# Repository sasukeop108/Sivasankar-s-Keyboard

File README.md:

# Sivasankar's keyboard
One day, I was thinking about making a custom keyboard which would be suitable for me from scratch but that was too costly. After i joined hackclub's stasis i thought why not to build our keyboard as the stasis event funds us. So i started making a custom 75 percent keyboard from scratch using fusion 360 and kicad. I used the layout keycool 84 which had 84 keys in it.
# Built keyboard

# Layout
.png)
# CAD

# PCB

# SCHEMATIC

# BOM
| Name | Purpose | Cost Per Item (USD) | Quantity | Total (USD) | Link | Distributor |
| :--- | :--- | :--- | :--- | :--- | :--- | :--- |
| 3d case | for housing keyboard | 8.50 | 1 | 8.50 | | printing legion |
| switches | for input to raspberry pi pico | 2.14 | 9 | 19.26 | [Cosmic Byte](https://www.thecosmicbyte.com/product/gateron-mechanical-switches-compatible-with-cosmic-byte-hot-swappable-keyboards-qty-1pc/) | cosmic byte |
| raspberry pi pico | for controlling everything | 0.00 | 1 | 0.00 | | self sourced |
| custom pcb | for soldering all components on | 40.65 | 1 | 40.65 | | jlcpcb |
| stabilizers | for bigger keycaps | 17.05 | 1 | 17.05 | [StacksKB](https://stackskb.com) | stackskb |
| keycaps | keys for typing | 13.89 | 1 | 13.89 | [StacksKB](https://stackskb.com/store/veekos-gradient-keycaps-cherry-profile-135-keys/) | stackskb |
| **Grand Total** | | | | **99.35** | | |
# Flashing instructions
download the keyboard.py from, the firmware folder and import it into circuit python select the com ports and youre ready to flash the code.

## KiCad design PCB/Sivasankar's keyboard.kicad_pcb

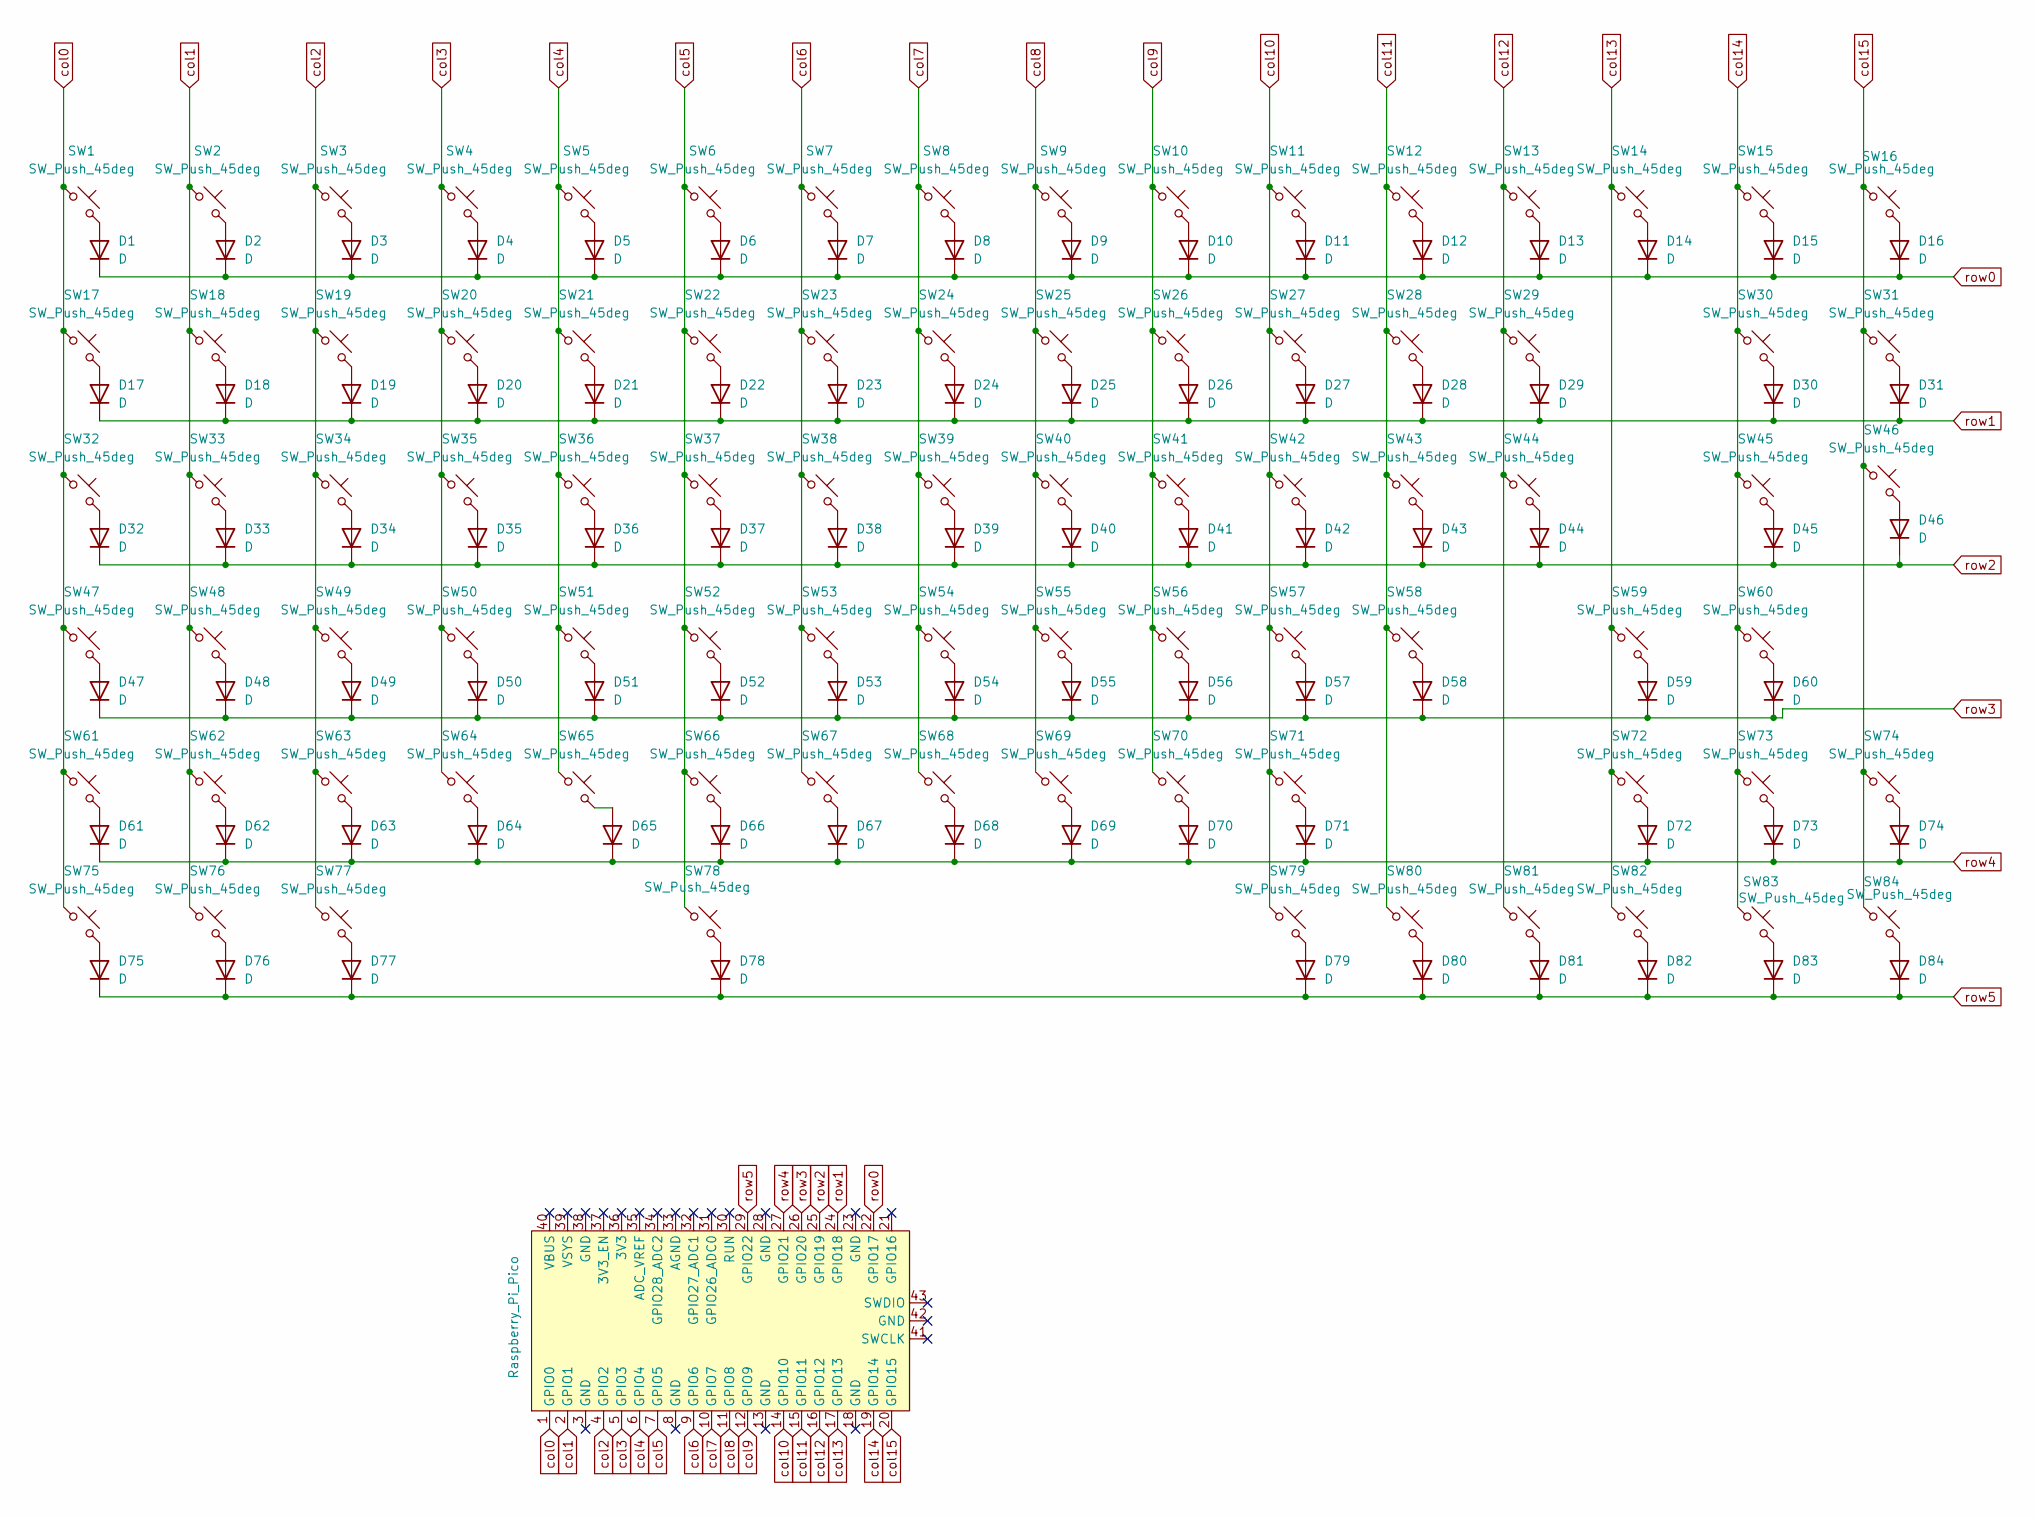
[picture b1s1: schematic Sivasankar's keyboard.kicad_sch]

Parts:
D1, D2, D3, D4, D5, D6, D7, D8, D9, D10, D11, D12, D13, D14, D15, D16, D17, D18, D19, D20, D21, D22, D23, D24, D25, D26, D27, D28, D29, D30, D31, D32, D33, D34, D35, D36, D37, D38, D39, D40, D41, D42, D43, D44, D45, D46, D47, D48, D49, D50, D51, D52, D53, D54, D55, D56, D57, D58, D59, D60, D61, D62, D63, D64, D65, D66, D67, D68, D69, D70, D71, D72, D73, D74, D75, D76, D77, D78, D79, D80, D81, D82, D83, D84: D; D_DO-35_SOD27_P7.62mm_Horizontal
SW1, SW2, SW3, SW4, SW5, SW6, SW7, SW8, SW9, SW10, SW11, SW12, SW13, SW14, SW15, SW16, SW17, SW18, SW19, SW20, SW21, SW22, SW23, SW24, SW25, SW26, SW27, SW28, SW29, SW30, SW31, SW32, SW33, SW34, SW35, SW36, SW37, SW38, SW39, SW40, SW41, SW42, SW43, SW44, SW45, SW46, SW47, SW48, SW49, SW50, SW51, SW52, SW53, SW54, SW55, SW56, SW57, SW58, SW59, SW60, SW61, SW62, SW63, SW64, SW65, SW66, SW67, SW68, SW69, SW70, SW71, SW72, SW73, SW74, SW75, SW76, SW77, SW78, SW79, SW80, SW81, SW82, SW83, SW84: SW_Push_45deg; SW_Cherry_MX_1.00u_PCB
U1: Raspberry_Pi_Pico; RaspberryPi_Pico_Common_THT

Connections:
unnamed: D1.2 (A), SW1.2
unnamed: D2.2 (A), SW2.2
unnamed: D3.2 (A), SW3.2
unnamed: D4.2 (A), SW4.2
unnamed: D5.2 (A), SW5.2
unnamed: D6.2 (A), SW6.2
unnamed: D7.2 (A), SW7.2
unnamed: D8.2 (A), SW8.2
unnamed: D9.2 (A), SW9.2
unnamed: D10.2 (A), SW10.2
unnamed: D11.2 (A), SW11.2
unnamed: D12.2 (A), SW12.2
unnamed: D13.2 (A), SW13.2
unnamed: D14.2 (A), SW14.2
unnamed: D15.2 (A), SW15.2
unnamed: D16.2 (A), SW16.2
unnamed: D17.2 (A), SW17.2
unnamed: D18.2 (A), SW18.2
unnamed: D19.2 (A), SW19.2
unnamed: D20.2 (A), SW20.2
unnamed: D21.2 (A), SW21.2
unnamed: D22.2 (A), SW22.2
unnamed: D23.2 (A), SW23.2
unnamed: D24.2 (A), SW24.2
unnamed: D25.2 (A), SW25.2
unnamed: D26.2 (A), SW26.2
unnamed: D27.2 (A), SW27.2
unnamed: D28.2 (A), SW28.2
unnamed: D29.2 (A), SW29.2
unnamed: D30.2 (A), SW30.2
unnamed: D31.2 (A), SW31.2
unnamed: D32.2 (A), SW32.2
unnamed: D33.2 (A), SW33.2
unnamed: D34.2 (A), SW34.2
unnamed: D35.2 (A), SW35.2
unnamed: D36.2 (A), SW36.2
unnamed: D37.2 (A), SW37.2
unnamed: D38.2 (A), SW38.2
unnamed: D39.2 (A), SW39.2
unnamed: D40.2 (A), SW40.2
unnamed: D41.2 (A), SW41.2
unnamed: D42.2 (A), SW42.2
unnamed: D43.2 (A), SW43.2
unnamed: D44.2 (A), SW44.2
unnamed: D45.2 (A), SW45.2
unnamed: D46.2 (A), SW46.2
unnamed: D47.2 (A), SW47.2
unnamed: D48.2 (A), SW48.2
unnamed: D49.2 (A), SW49.2
unnamed: D50.2 (A), SW50.2
unnamed: D51.2 (A), SW51.2
unnamed: D52.2 (A), SW52.2
unnamed: D53.2 (A), SW53.2
unnamed: D54.2 (A), SW54.2
unnamed: D55.2 (A), SW55.2
unnamed: D56.2 (A), SW56.2
unnamed: D57.2 (A), SW57.2
unnamed: D58.2 (A), SW58.2
unnamed: D59.2 (A), SW59.2
unnamed: D60.2 (A), SW60.2
unnamed: D61.2 (A), SW61.2
unnamed: D62.2 (A), SW62.2
unnamed: D63.2 (A), SW63.2
unnamed: D64.2 (A), SW64.2
unnamed: D65.2 (A), SW65.2
unnamed: D66.2 (A), SW66.2
unnamed: D67.2 (A), SW67.2
unnamed: D68.2 (A), SW68.2
unnamed: D69.2 (A), SW69.2
unnamed: D70.2 (A), SW70.2
unnamed: D71.2 (A), SW71.2
unnamed: D72.2 (A), SW72.2
unnamed: D73.2 (A), SW73.2
unnamed: D74.2 (A), SW74.2
unnamed: D75.2 (A), SW75.2
unnamed: D76.2 (A), SW76.2
unnamed: D77.2 (A), SW77.2
unnamed: D78.2 (A), SW78.2
unnamed: D79.2 (A), SW79.2
unnamed: D80.2 (A), SW80.2
unnamed: D81.2 (A), SW81.2
unnamed: D82.2 (A), SW82.2
unnamed: D83.2 (A), SW83.2
unnamed: D84.2 (A), SW84.2
col0: SW1.1, SW17.1, SW32.1, SW47.1, SW61.1, SW75.1, U1.1 (GPIO0)
col1: SW2.1, SW18.1, SW33.1, SW48.1, SW62.1, SW76.1, U1.2 (GPIO1)
col2: SW3.1, SW19.1, SW34.1, SW49.1, SW63.1, SW77.1, U1.4 (GPIO2)
col3: SW4.1, SW20.1, SW35.1, SW50.1, SW64.1, U1.5 (GPIO3)
col4: SW5.1, SW21.1, SW36.1, SW51.1, SW65.1, U1.6 (GPIO4)
col5: SW6.1, SW22.1, SW37.1, SW52.1, SW66.1, SW78.1, U1.7 (GPIO5)
col6: SW7.1, SW23.1, SW38.1, SW53.1, SW67.1, U1.9 (GPIO6)
col7: SW8.1, SW24.1, SW39.1, SW54.1, SW68.1, U1.10 (GPIO7)
col8: SW9.1, SW25.1, SW40.1, SW55.1, SW69.1, U1.11 (GPIO8)
col9: SW10.1, SW26.1, SW41.1, SW56.1, SW70.1, U1.12 (GPIO9)
col10: SW11.1, SW27.1, SW42.1, SW57.1, SW71.1, SW79.1, U1.14 (GPIO10)
col11: SW12.1, SW28.1, SW43.1, SW58.1, SW80.1, U1.15 (GPIO11)
col12: SW13.1, SW29.1, SW44.1, SW81.1, U1.16 (GPIO12)
col13: SW14.1, SW59.1, SW72.1, SW82.1, U1.17 (GPIO13)
col14: SW15.1, SW30.1, SW45.1, SW60.1, SW73.1, SW83.1, U1.19 (GPIO14)
col15: SW16.1, SW31.1, SW46.1, SW74.1, SW84.1, U1.20 (GPIO15)
row0: D1.1 (K), D2.1 (K), D3.1 (K), D4.1 (K), D5.1 (K), D6.1 (K), D7.1 (K), D8.1 (K), D9.1 (K), D10.1 (K), D11.1 (K), D12.1 (K), D13.1 (K), D14.1 (K), D15.1 (K), D16.1 (K), U1.22 (GPIO17)
row1: D17.1 (K), D18.1 (K), D19.1 (K), D20.1 (K), D21.1 (K), D22.1 (K), D23.1 (K), D24.1 (K), D25.1 (K), D26.1 (K), D27.1 (K), D28.1 (K), D29.1 (K), D30.1 (K), D31.1 (K), U1.24 (GPIO18)
row2: D32.1 (K), D33.1 (K), D34.1 (K), D35.1 (K), D36.1 (K), D37.1 (K), D38.1 (K), D39.1 (K), D40.1 (K), D41.1 (K), D42.1 (K), D43.1 (K), D44.1 (K), D45.1 (K), D46.1 (K), U1.25 (GPIO19)
row3: D47.1 (K), D48.1 (K), D49.1 (K), D50.1 (K), D51.1 (K), D52.1 (K), D53.1 (K), D54.1 (K), D55.1 (K), D56.1 (K), D57.1 (K), D58.1 (K), D59.1 (K), D60.1 (K), U1.26 (GPIO20)
row4: D61.1 (K), D62.1 (K), D63.1 (K), D64.1 (K), D65.1 (K), D66.1 (K), D67.1 (K), D68.1 (K), D69.1 (K), D70.1 (K), D71.1 (K), D72.1 (K), D73.1 (K), D74.1 (K), U1.27 (GPIO21)
row5: D75.1 (K), D76.1 (K), D77.1 (K), D78.1 (K), D79.1 (K), D80.1 (K), D81.1 (K), D82.1 (K), D83.1 (K), D84.1 (K), U1.29 (GPIO22)

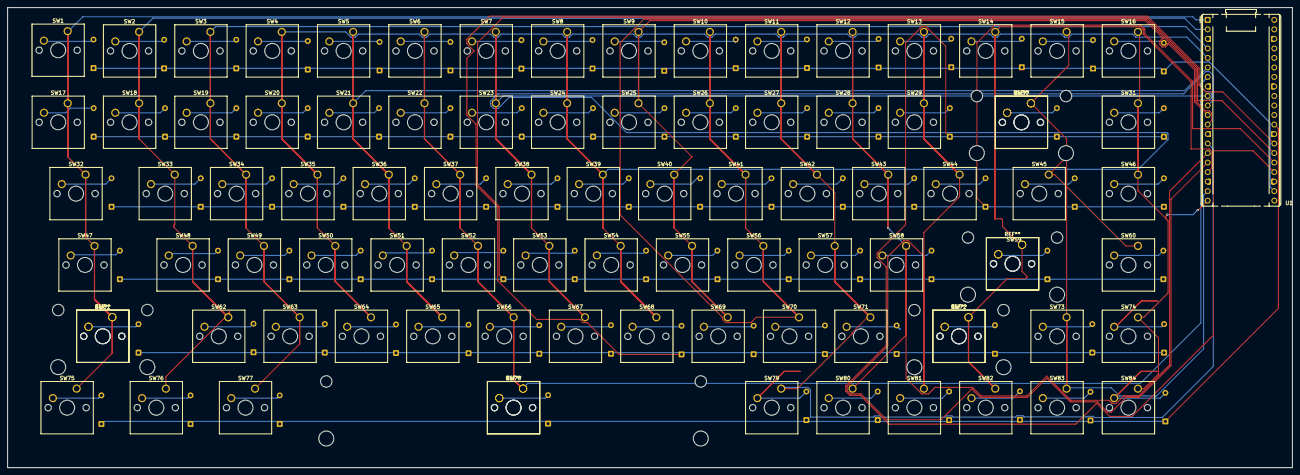
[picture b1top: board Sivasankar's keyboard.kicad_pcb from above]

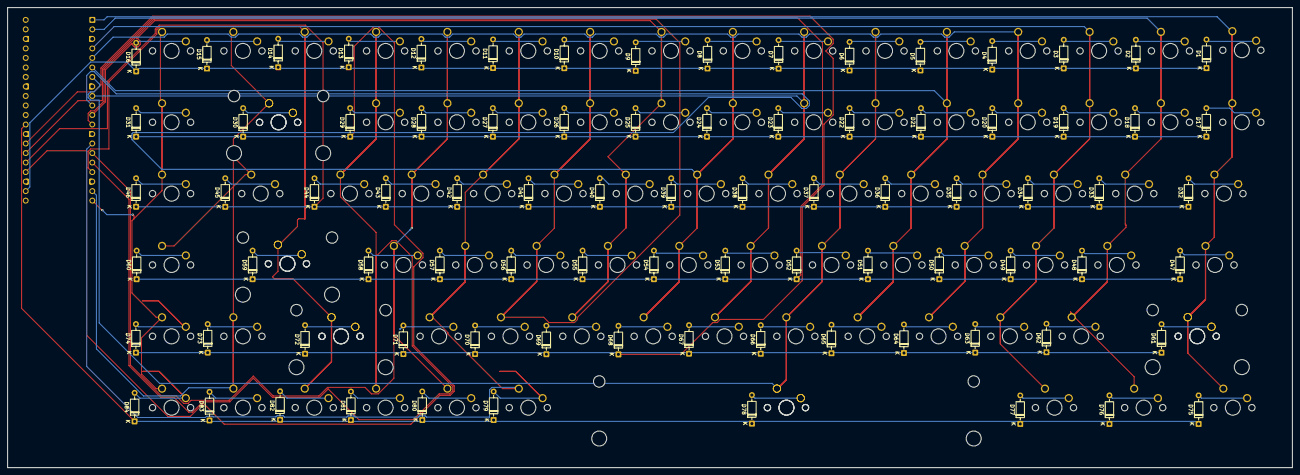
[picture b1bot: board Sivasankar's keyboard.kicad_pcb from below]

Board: 2 copper layers, 343.0 x 122.8 mm, 169 parts (84 on the bottom side), 106 nets.

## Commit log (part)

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2026-03-20 Create J
2026-03-20 Create G
2026-03-20 Rename ss.png to assembly.png
2026-03-20 Create D
2026-03-20 Create s
2026-03-20 Create r
2026-03-20 Rename jlcc0.png to jlc1.png
2026-03-20 Rename jlc1.png to jlcshipping.png
2026-03-20 Rename sssss.png to StacksKB.png
2026-03-20 Rename jll.png to jlc1.png
2026-03-20 Rename jll.png to jlc2.png
